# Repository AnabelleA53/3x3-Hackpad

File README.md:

## My Macropad
myMacropad is a personal project I made for Hack Club Blueprint. It uses a 3x3 keyboard with a rotary encoder. It uses a Seeed XIAO RP2040 and QMK firmware.

## Features
- 2-part 3D-printed case
- EC11 Rotary encoder
- 9 Keys

## CAD Model:
The case fits together using 4 M3 Bolts that fit through the case and PCB. It comes in two pieces - the top and bottom of the case. On the top of the case is 
engraved "per aspera ad astra", meaning "through tough times, to the stars" (ignore how I got the word order in the phrases wrong) (as a Latin kid I can vet 
word order doesn't matter in Latin anyway!!!)

## PCB:
This PCB was made using KiCad!

Schematic:

PCB

Specific footprints can be found in the extras folder in the pcb folder.

## Firmware Overview
This macropad uses QMK firmware for everything. However, it's not flashed yet because I don't actually have the PCB yet!

## BOM:
Everything you need to make this macropad:
- 9x MX-Style Switches
- 9x DSA Keycaps
- 1 x EC11 Rotary encoder
- 4x M3x16mm screws
- 4x M3 bolts
- 1 unsoldered Seeed XIAO RP2040
- 10x through-hole 1N4148 Diodes

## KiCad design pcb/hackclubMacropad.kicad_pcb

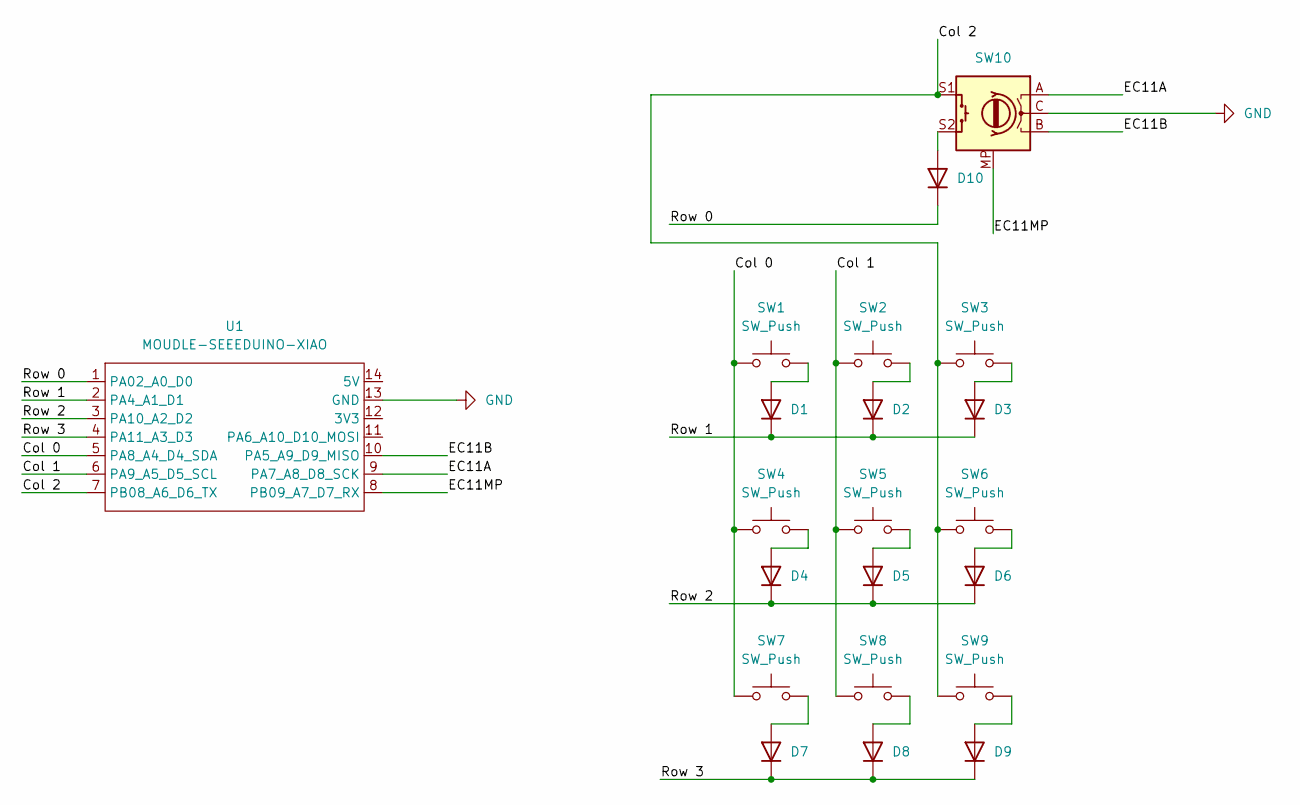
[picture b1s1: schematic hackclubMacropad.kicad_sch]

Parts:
D1, D2, D3, D4, D5, D6, D7, D8, D9, D10: 1N4148; D_DO-35_SOD27_P7.62mm_Horizontal
SW1, SW2, SW3, SW4, SW5, SW6, SW7, SW8, SW9: SW_Push; SW_Cherry_MX_1.00u_PCB
SW10: RotaryEncoder_Switch_MP; RotaryEncoder_Alps_EC11E-Switch_Vertical_H20mm
U1: MOUDLE-SEEEDUINO-XIAO; XIAO-Generic-Hybrid-14P-2.54-21X17.8MM

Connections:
/Col 0: SW1.1, SW4.1, SW7.1, U1.5 (PA8_A4_D4_SDA)
/Col 1: SW2.1, SW5.1, SW8.1, U1.6 (PA9_A5_D5_SCL)
/Col 2: SW3.1, SW6.1, SW9.1, SW10.S1, U1.7 (PB08_A6_D6_TX)
/EC11A: SW10.A, U1.9 (PA7_A8_D8_SCK)
/EC11B: SW10.B, U1.10 (PA5_A9_D9_MISO)
/Row 0: D10.1 (K), U1.1 (PA02_A0_D0)
/Row 1: D1.1 (K), D2.1 (K), D3.1 (K), U1.2 (PA4_A1_D1)
/Row 2: D4.1 (K), D5.1 (K), D6.1 (K), U1.3 (PA10_A2_D2)
/Row 3: D7.1 (K), D8.1 (K), D9.1 (K), U1.4 (PA11_A3_D3)
GND: SW10.C, U1.13 (GND)
unnamed: D1.2 (A), SW1.2
unnamed: D2.2 (A), SW2.2
unnamed: D3.2 (A), SW3.2
unnamed: D4.2 (A), SW4.2
unnamed: D5.2 (A), SW5.2
unnamed: D6.2 (A), SW6.2
unnamed: D7.2 (A), SW7.2
unnamed: D8.2 (A), SW8.2
unnamed: D9.2 (A), SW9.2
unnamed: D10.2 (A), SW10.S2

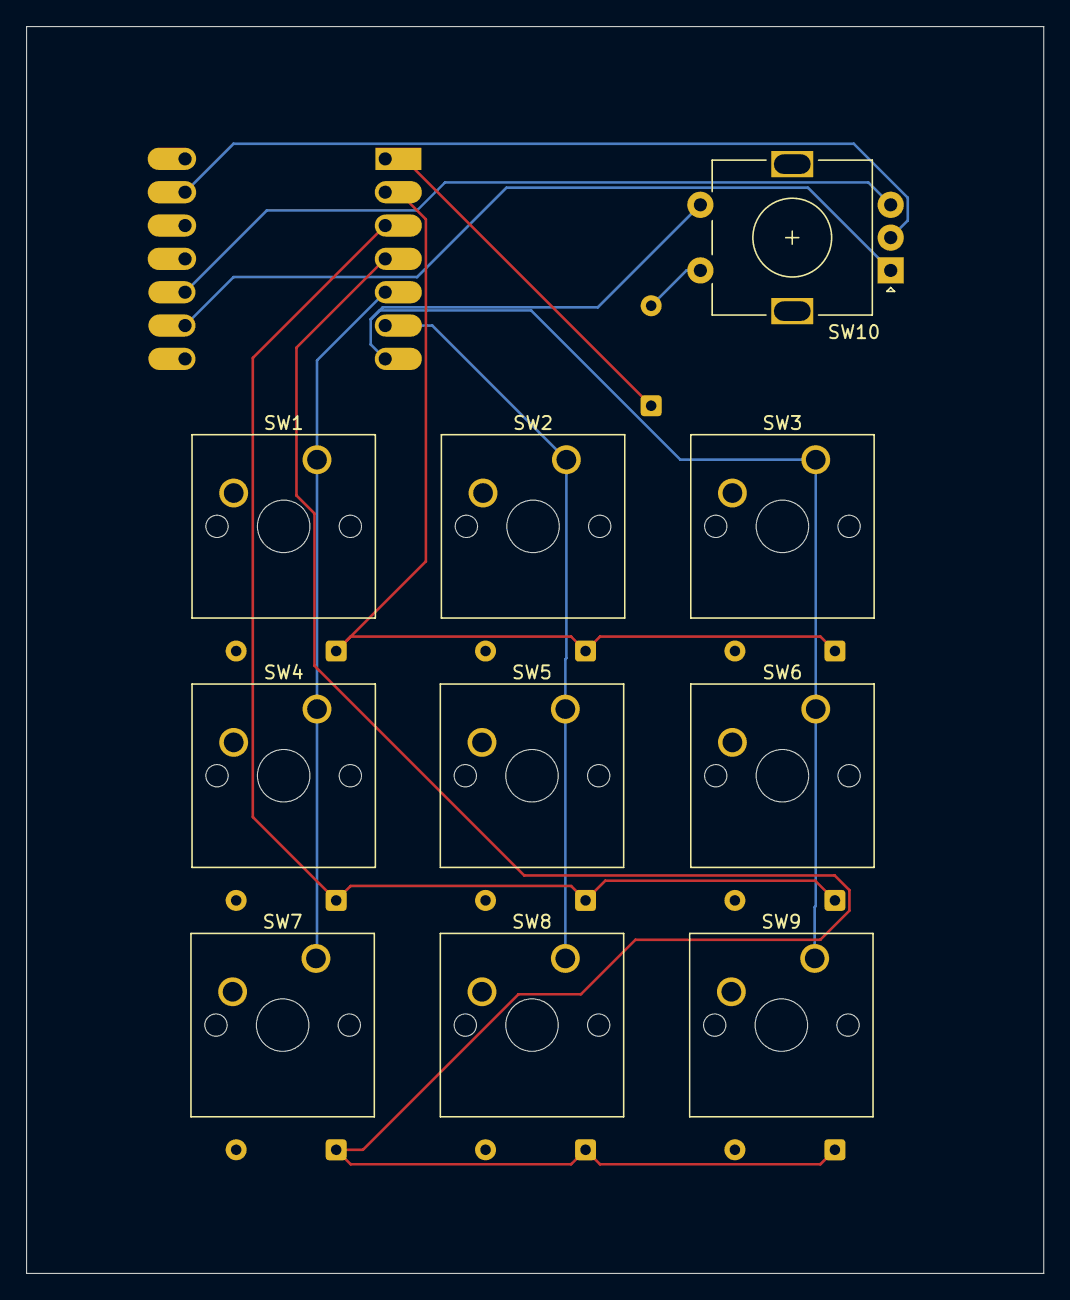
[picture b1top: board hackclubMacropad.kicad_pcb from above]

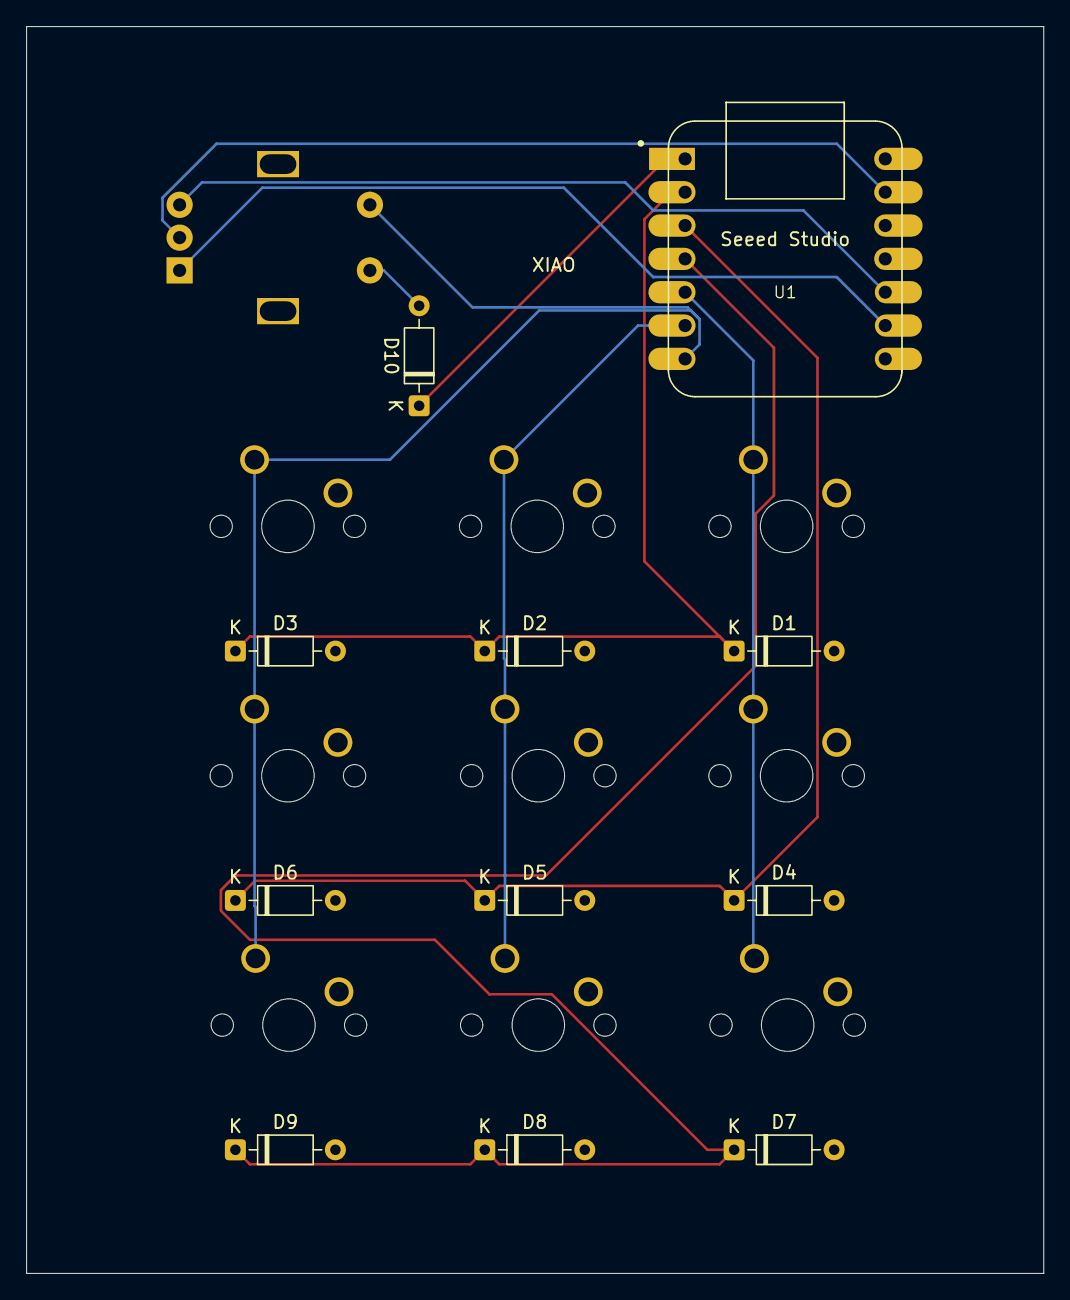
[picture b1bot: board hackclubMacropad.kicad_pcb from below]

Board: 2 copper layers, 77.5 x 95.0 mm, 21 parts (11 on the bottom side), 20 nets.

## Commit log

2026-03-03 added mostly completed kicad files
    missing 3d components in footprints
2026-03-04 added some 3d models to footprints
2026-03-05 added footprints and downloaded step file
    created cad folder
2026-03-05 added footprints
2026-03-05 finished macropad case and assembly
2026-03-05 reorganized and added qmk firmware
2026-03-05 Add README
    Added detailed project description, features, CAD model, PCB information, firmware overview, and BOM for the Macropad.
2026-03-05 edited README
2026-03-05 added production folder and files and organized
2026-03-06 added f3d and 3mf files and edited pcb
2026-03-06 updated pcb to not connect mounting pin
2026-03-06 updated keymaps and took out 3mf file
2026-03-06 Edited README
    Updated images in README with new screenshots.
2026-03-06 commit autosaved files from pcb
